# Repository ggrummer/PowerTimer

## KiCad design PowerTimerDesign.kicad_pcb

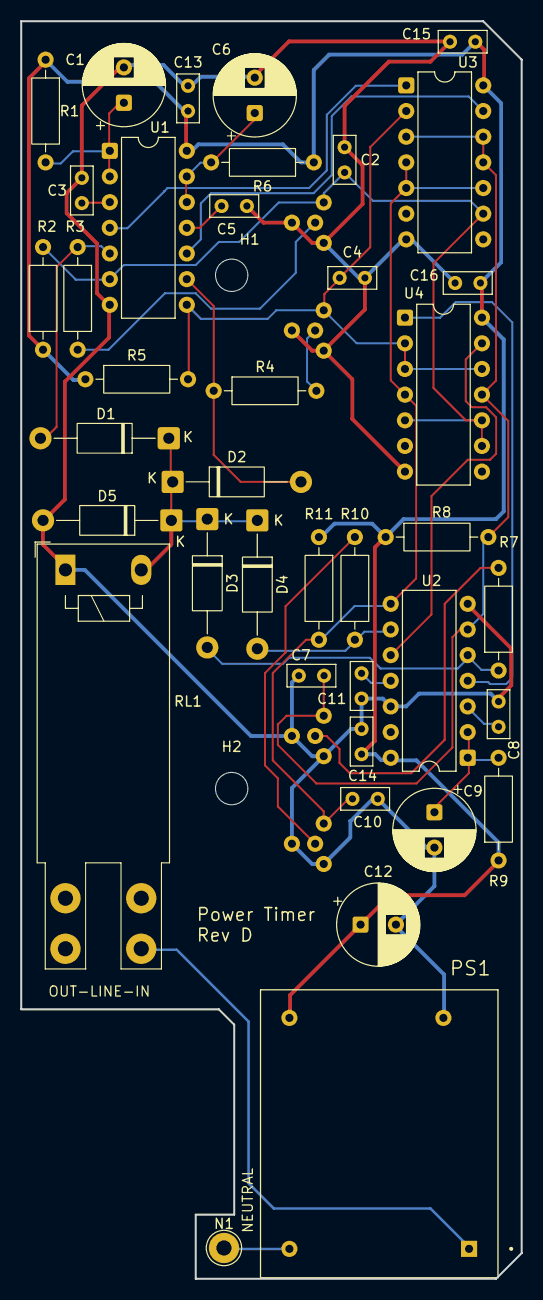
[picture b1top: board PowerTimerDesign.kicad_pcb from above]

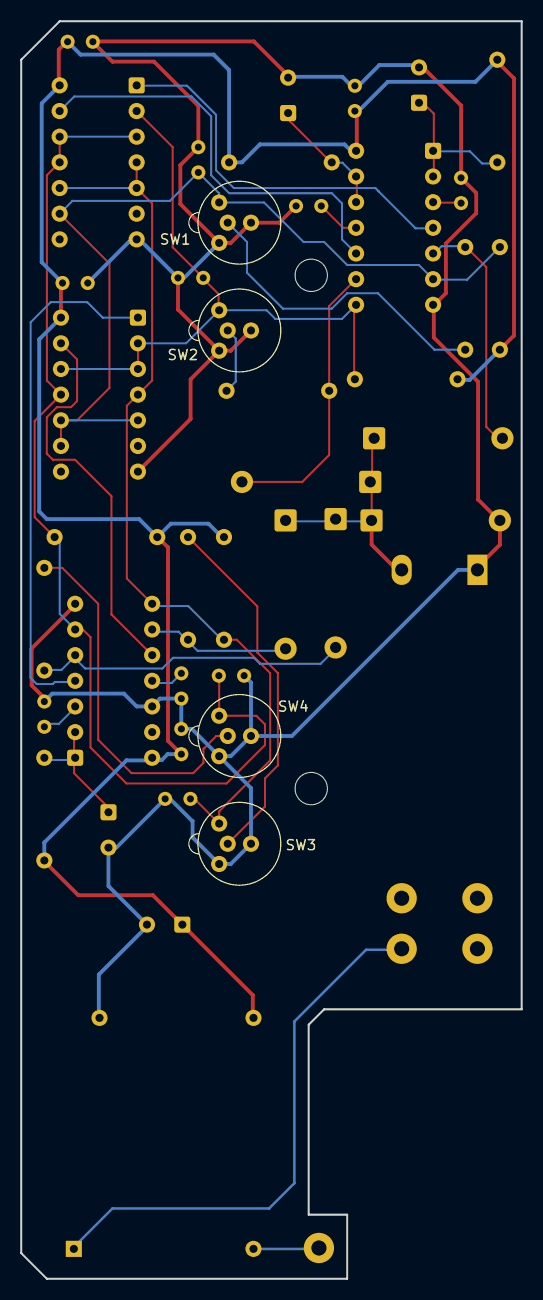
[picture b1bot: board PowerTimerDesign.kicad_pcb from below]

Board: 2 copper layers, 49.5 x 124.5 mm, 45 parts (4 on the bottom side), 28 nets.

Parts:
C1, C6, C9, C12: 270uF, 25V; CP_Radial_D8.0mm_P3.50mm
C2, C4, C7, C10, C13, C14, C15, C16: 0.1uF; C_Rect_L4.6mm_W2.0mm_P2.50mm_MKS02_FKP02
C3, C5, C8, C11: 0.01uF; C_Rect_L4.6mm_W2.0mm_P2.50mm_MKS02_FKP02
D1, D2, D3, D4: 1N5817; D_DO-41_SOD81_P12.70mm_Horizontal
D5: 1N5060; D_DO-41_SOD81_P12.70mm_Horizontal
H1: MountingHole; MountingHole_3.2mm_M3_DIN965
H2: MountingHole; MountingHole_3.2mm_M3
N1: TestPoint; TestPoint_THTPad_D3.0mm_Drill1.5mm
PS1: RAC03-12SK; CONV_RAC03-12SK
R1: 1M; R_Axial_DIN0207_L6.3mm_D2.5mm_P10.16mm_Horizontal
R2, R5, R8, R11: 4.7K; R_Axial_DIN0207_L6.3mm_D2.5mm_P10.16mm_Horizontal
R3, R4, R7, R10: 680; R_Axial_DIN0207_L6.3mm_D2.5mm_P10.16mm_Horizontal
R6: 2M; R_Axial_DIN0207_L6.3mm_D2.5mm_P10.16mm_Horizontal
R9: 12.1M; R_Axial_DIN0207_L6.3mm_D2.5mm_P10.16mm_Horizontal
RL1: AZ762FV-1AE-12DF; Relay_SPST_Zettler_AZ762F
SW1, SW2, SW3, SW4: 0041_9146_3317; Schurter_SPST_LDT
U1, U2: NE556; DIP-14_W7.62mm
U3, U4: 4082; DIP-14_W7.62mm

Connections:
+12V: C12.1, C13.1, C14.1, C15.1, C16.1, PS1.3 (+VOUT), R1.1, R2.1, R5.1, R6.1, R8.1, R9.1, R11.1, U1.14 (VCC), U2.14 (VCC), U3.14 (Vdd), U4.14 (Vdd)
/Power/DRV5: D1.2 (A), R3.1, U1.5 (Q)
/Power/DRV10: D2.2 (A), R4.1, U1.9 (Q)
/Power/DRV60: D3.2 (A), R7.1, U2.5 (Q)
/Power/DRVON: D4.2 (A), R10.1, U2.9 (Q)
/Power/LINEIN: PS1.1 (VAC_IN(L)), RL1.4
/Timers/LED5: R3.2, SW1.6 (A)
/Timers/LED10: R4.2, SW2.6 (A)
/Timers/LED60: R7.2, SW4.6 (A)
/Timers/LEDON: R10.2, SW3.6 (A)
/Timers/RST5: U1.4 (R), U3.1
/Timers/RST10: U1.10 (R), U3.13
/Timers/RST60: U2.4 (R), U4.1
/Timers/RSTON: U2.10 (R), U4.13
/Timers/SET5: C2.1, R2.2, SW1.2, U1.6 (TR), U3.9, U4.5, U4.9, U4.10
/Timers/SET10: C4.1, R5.2, SW2.2, U1.8 (TR), U3.2, U4.2, U4.3, U4.12
/Timers/SET60: C7.1, R8.2, SW4.2, U2.6 (TR), U3.3, U3.11, U3.12, U4.11
/Timers/SETON: C10.1, R11.2, SW3.2, U2.8 (TR), U3.4, U3.5, U3.10, U4.4
/Timers/TIME5: C1.1, R1.2, U1.1 (DIS), U1.2 (THR)
/Timers/TIME10: C6.1, R6.2, U1.12 (THR), U1.13 (DIS)
/Timers/TIME60: C9.1, R9.2, U2.1 (DIS), U2.2 (THR)
GND: C1.2, C2.2, C3.2, C4.2, C5.2, C6.2, C7.2, C8.2, C9.2, C10.2, C11.2, C12.2, C13.2, C14.2, C15.2, C16.2, D5.2 (A), PS1.2 (-VOUT), RL1.1, SW1.1, SW1.5 (K), SW2.1, SW2.5 (K), SW3.1, SW3.5 (K), SW4.1, SW4.5 (K), U1.7 (GND), U2.7 (GND), U2.12 (THR), U3.7 (Vss), U4.7 (Vss)
unnamed: D1.1 (K), D2.1 (K), D3.1 (K), D4.1 (K), D5.1 (K), RL1.6
unnamed: N1.1, PS1.4 (VAC_IN(N))
unnamed: C3.1, U1.3 (CV)
unnamed: C5.1, U1.11 (CV)
unnamed: C8.1, U2.3 (CV)
unnamed: C11.1, U2.11 (CV)

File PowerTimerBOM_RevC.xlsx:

Power Timer Assembly Parts Lists
Top Level Parts List
Description |  | Qty | Manufacturer | Part Number | Distributer
Power Block, 4 Outlet |  | 1 | Commercial Electric | 1007 546 208 | Home Depot
Screw, 4-40, 5/8" Long |  | 2 |  | 91772A112 | McMaster-Carr
Heat-Set Inserts for Plastic, Stainless Steel, 4-40 |  | 2 |  | 94459A426 | McMaster-Carr
Spacer Top |  | 1 | 3D Printed | Spacer Top2.stl
Spacer Bottom |  | 1 | 3D Printed | Spacer Bot.stl
Push Button Holder |  | 2 | 3D Printed | PushButHold.stl
Power Timer PCB Rev C |  | 1 | OSH Park or your choice | PowerTimerDesign.kicad_pcb
PCB Parts List |  |  |  |  | Rev C
Description | Reference | Qty | Manufacturer | Part Number | Distributer
Cap 270uF, 25V, Alum, Radial | C1,C6,C9,C12 | 4 | PANASONIC ELECTRONIC | EEU-FK1E271 | Digi-Key
Cap 0.1uF, 50V X7R, Radial | C2,C4,C7,C10,C13,C14,C15,C16 | 8 | Kemet | C326C104K5R5TA7301 | Digi-Key
Cap 0.01uF, 50V X7R, Radial | C3,C5,C8,C11 | 4 | Kemet | C316C103K5R5TA7301 | Digi-Key
Diode, Schottky, Axial, 1A, 20V | D1,D2,D3,D4 | 4 | MCC | 1N5817-TP | Digi-Key
Diode, Axial, 2A, 400V | D5 | 1 | Vishay Semiconductor | 1N5060TR | Digi-Key
AC/DC Converter 12V 3W | PS1 | 1 | RECOM POWER | RAC03-12SK | Digi-Key
Res, 1M, 1%, 1/4W | R1 | 1 | YAGEO | MFR-25FBF52-1M | Digi-Key
Res, 4.7K, 5%, 1/4W | R2,R5,R8,R11 | 4 | Stackpole | CF14JT4K70 | Digi-Key
Res, 680, 5%, 1/4W | R3,R4,R7,R10 | 4 | Stackpole | CF14JT680R | Digi-Key
Res, 2M, 1%, 1/4W | R6 | 1 | YAGEO | MFR-25FBF52-2M | Digi-Key
Res, 12.1M, 1%, 1/4W | R9 | 1 | KOA SPEER ELECTRONICS | RK1/4DCT52R1215F | Digi-Key
Relay, SPST 20A 12V | RL1 | 1 | AMERICAN ZETTLER | AZ762FV-1AE-12DF | Digi-Key
Switch, Push Button, Illumined | SW1,SW2,SW3,SW4 | 4 | SCHURTER | 0041.9146.3317 | Digi-Key
Timer, Dual, DIP14 | U1,U2 | 2 | TEXAS INSTRUMENTS | NE556N | Digi-Key
NAND Gate, 4-Input, Dual, DIP14 | U3,U4 | 2 | TEXAS INSTRUMENTS | CD4082BE | Digi-Key

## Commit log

2026-03-17 Initial entry of project files
2026-03-17 Project description file in PDF form
    Added PDF version of project description file.
2026-03-23 Added schematic for PCB
    Added the schematic for the Power Timer PCB.
2026-03-26 Replaced Rev C design with Rev D
    Swapped R10 & R11 Ref Des (they were on the wrong resistor).
    Rewired SW3 and SW4 so their functions would be swapped (so on Rev D, the order on the unit is now: Stay On, 1 Hour, 10 Minutes & 5 Minutes)
